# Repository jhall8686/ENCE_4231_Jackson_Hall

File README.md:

# ENCE_4231_Jackson_Hall
Embedded Systems Repository

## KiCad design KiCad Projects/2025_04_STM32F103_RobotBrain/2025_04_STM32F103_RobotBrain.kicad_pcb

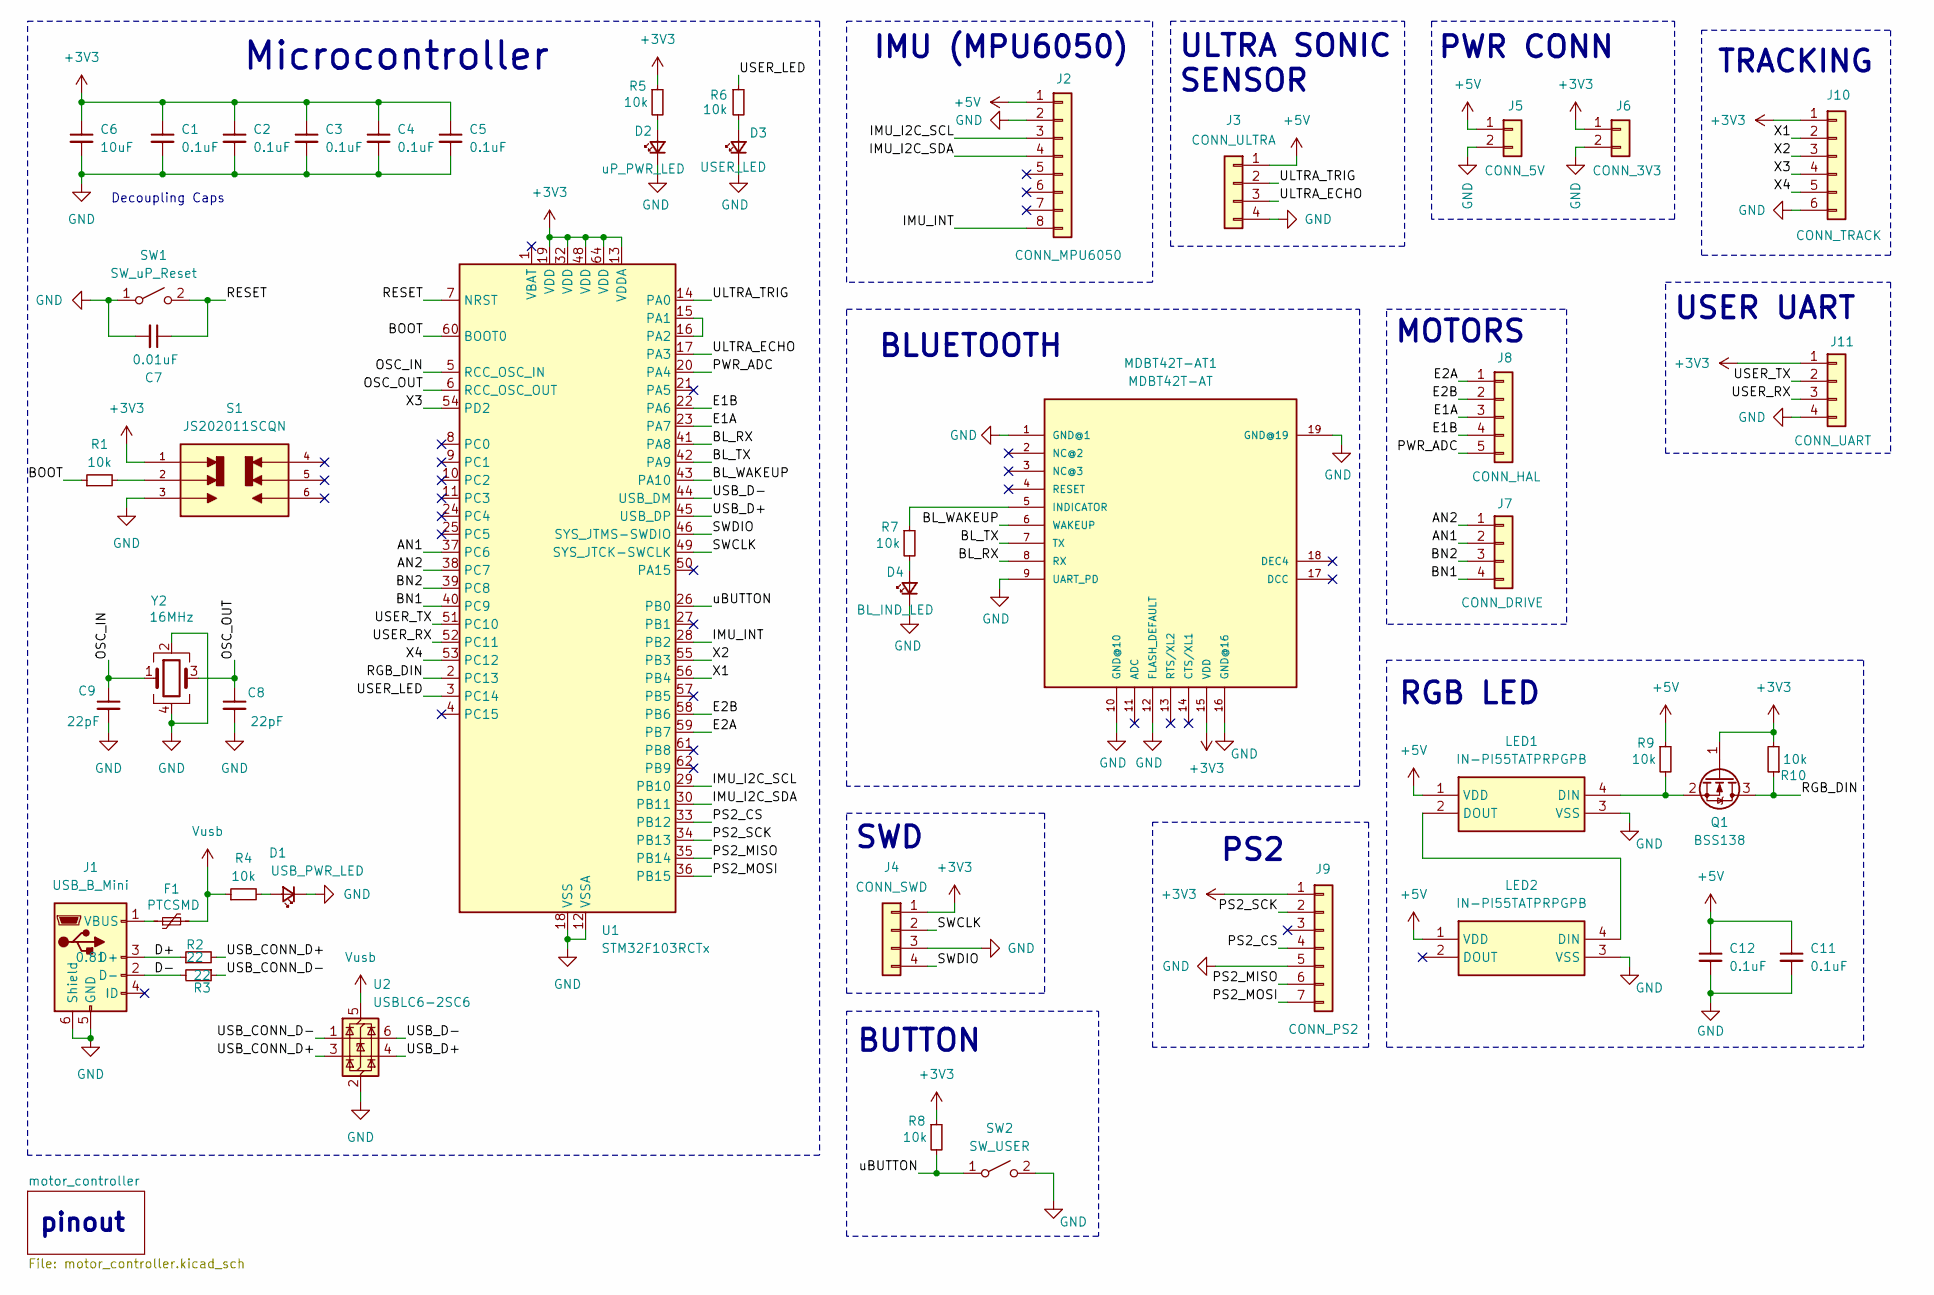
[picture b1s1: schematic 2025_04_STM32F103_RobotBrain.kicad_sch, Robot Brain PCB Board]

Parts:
C1, C2, C3, C4, C5, C11, C12: 0.1uF; C_0805_2012Metric_Pad1.18x1.45mm_HandSolder; Mfr #P KAM21BR71H104JT
C6: 10uF; C_0805_2012Metric_Pad1.18x1.45mm_HandSolder; Mfr #P LMK212ABJ106KG-T
C7: 0.01uF; C_0805_2012Metric_Pad1.18x1.45mm_HandSolder; Mfr #P KAF21BR72A103JT
C8, C9: 22pF; C_0805_2012Metric_Pad1.18x1.45mm_HandSolder; Mfr #P 0805ZA220JAT2A
D1: USB_PWR_LED; LED_0805_2012Metric_Pad1.15x1.40mm_HandSolder; Mfr #P 150080VS75000
D2: uP_PWR_LED; LED_0805_2012Metric_Pad1.15x1.40mm_HandSolder; Mfr #P 150080VS75000
D3: USER_LED; LED_0805_2012Metric_Pad1.15x1.40mm_HandSolder; Mfr #P 150080RS75000
D4: BL_IND_LED; LED_0805_2012Metric_Pad1.15x1.40mm_HandSolder; Mfr #P 150080VS75000
F1: PTCSMD; Fuse_0805_2012Metric_Pad1.15x1.40mm_HandSolder; Mfr #P 0ZCK0050AF2E
J1: USB_B_Mini; USB_Mini-B_Lumberg_2486_01_Horizontal; Mfr #P UJ2-MBH-4-SMT-TR
J2: CONN_MPU6050; PinSocket_1x08_P2.54mm_Vertical
J3: CONN_ULTRA; PinSocket_1x04_P2.54mm_Vertical
J4: CONN_SWD; PinSocket_1x04_P2.54mm_Vertical
J5: CONN_5V; JST_XH_B2B-XH-A_1x02_P2.50mm_Vertical
J6: CONN_3V3; JST_XH_B2B-XH-A_1x02_P2.50mm_Vertical
J7: CONN_DRIVE; JST_XH_B4B-XH-A_1x04_P2.50mm_Vertical
J8: CONN_HAL; JST_XH_B5B-XH-A_1x05_P2.50mm_Vertical
J9: CONN_PS2; PinHeader_1x07_P2.54mm_Vertical
J10: CONN_TRACK; JST_XH_B6B-XH-A_1x06_P2.50mm_Vertical
J11: CONN_UART; JST_XH_B4B-XH-A_1x04_P2.50mm_Vertical
LED1, LED2: IN-PI55TATPRPGPB; INPI55TATPRPGPB; Manufacturer_Part_Number IN-PI55TATPRPGPB; Mouser Part Number 743-IN-PI55TATPRPGPB
MDBT42T-AT1: MDBT42T-AT; MDBT42T
Q1: BSS138; SOT-23; Mfr #P BSS138
R1, R4, R5, R6, R7, R8, R9, R10: 10k; R_0805_2012Metric_Pad1.20x1.40mm_HandSolder; Mfr #P RK73B2ATTE103J
R2, R3: 22; R_0805_2012Metric_Pad1.20x1.40mm_HandSolder; Mfr #P RC0805FR-7W22RL
S1: JS202011SCQN; SW_uP_Boot; PARTREV 26 May 22
SW1: SW_uP_Reset; Mfr #P 434121025816
SW2: SW_USER; SW_SPST_PTS647_Sx50; Mfr #P TL3305BF100QG
U1: STM32F103RCTx; LQFP-64_10x10mm_P0.5mm; Mfr #P STM32F103RCT6
U2: USBLC6-2SC6; SOT-23-6; Mfr #P USBLC6-2SC6
Y2: 16MHz; Crystal_SMD_Abracon_ABM8G-4Pin_3.2x2.5mm; Mfr #P ABM8-16.000MHZ-D1X-T

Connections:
+3V3: C1.1, C2.1, C3.1, C4.1, C5.1, C6.1, J4.1, J6.1, J9.1, J10.1, J11.1, MDBT42T-AT1.15 (VDD), Q1.1 (G), R5.1, R8.1, R10.2, S1.1, U1.13 (VDDA), U1.19 (VDD), U1.32 (VDD), U1.48 (VDD), U1.64 (VDD)
+5V: C11.1, C12.1, J2.1, J3.1, J5.1, LED1.1 (VDD), LED2.1 (VDD), R9.1
/AN1: J7.2, U1.37 (PC6)
/AN2: J7.1, U1.38 (PC7)
/BL_RX: MDBT42T-AT1.8 (RX), U1.41 (PA8)
/BL_TX: MDBT42T-AT1.7 (TX), U1.42 (PA9)
/BL_WAKEUP: MDBT42T-AT1.6 (WAKEUP), U1.43 (PA10)
/BN1: J7.4, U1.40 (PC9)
/BN2: J7.3, U1.39 (PC8)
/BOOT: R1.1, U1.60 (BOOT0)
/D+: J1.3 (D+), R2.1
/D-: J1.2 (D-), R3.2
/E1A: J8.3, U1.23 (PA7)
/E1B: J8.4, U1.22 (PA6)
/E2A: J8.1, U1.59 (PB7)
/E2B: J8.2, U1.58 (PB6)
/IMU_I2C_SCL: J2.3, U1.29 (PB10)
/IMU_I2C_SDA: J2.4, U1.30 (PB11)
/IMU_INT: J2.8, U1.28 (PB2)
/OSC_IN: C9.1, U1.5 (RCC_OSC_IN), Y2.1
/OSC_OUT: C8.1, U1.6 (RCC_OSC_OUT), Y2.3
/PS2_CS: J9.4, U1.33 (PB12)
/PS2_MISO: J9.6, U1.35 (PB14)
/PS2_MOSI: J9.7, U1.36 (PB15)
/PS2_SCK: J9.2, U1.34 (PB13)
/PWR_ADC: J8.5, U1.20 (PA4)
/RESET: C7.1, SW1.2 (B), U1.7 (NRST)
/RGB_DIN: Q1.3 (D), R10.1, U1.2 (PC13)
/SWCLK: J4.2, U1.49 (SYS_JTCK-SWCLK)
/SWDIO: J4.4, U1.46 (SYS_JTMS-SWDIO)
/ULTRA_ECHO: J3.3, U1.17 (PA3)
/ULTRA_TRIG: J3.2, U1.14 (PA0)
/USB_CONN_D+: R2.2, U2.3 (I/O2)
/USB_CONN_D-: R3.1, U2.1 (I/O1)
/USB_D+: U1.45 (USB_DP), U2.4 (I/O2)
/USB_D-: U1.44 (USB_DM), U2.6 (I/O1)
/USER_LED: R6.1, U1.3 (PC14)
/USER_RX: J11.3, U1.52 (PC11)
/USER_TX: J11.2, U1.51 (PC10)
/X1: J10.2, U1.56 (PB4)
/X2: J10.3, U1.55 (PB3)
/X3: J10.4, U1.54 (PD2)
/X4: J10.5, U1.53 (PC12)
/uBUTTON: R8.2, SW2.1 (A), U1.26 (PB0)
GND: C1.2, C2.2, C3.2, C4.2, C5.2, C6.2, C7.2, C8.2, C9.2, C11.2, C12.2, D1.1 (K), D2.1 (K), D3.1 (K), D4.1 (K), J1.5 (GND), J1.6 (Shield), J2.2, J3.4, J4.3, J5.2, J6.2, J9.5, J10.6, J11.4, LED1.3 (VSS), LED2.3 (VSS), MDBT42T-AT1.1 (GND@1), MDBT42T-AT1.9 (UART_PD), MDBT42T-AT1.10 (GND@10), MDBT42T-AT1.12 (FLASH_DEFAULT), MDBT42T-AT1.16 (GND@16), MDBT42T-AT1.19 (GND@19), S1.3, SW1.1 (A), SW2.2 (B), U1.12 (VSSA), U1.18 (VSS), U1.31 (VSS), U1.47 (VSS), U1.63 (VSS), U2.2 (GND), Y2.2, Y2.4
unnamed: D1.2 (A), R4.2
unnamed: D2.2 (A), R5.2
unnamed: D3.2 (A), R6.2
unnamed: D4.2 (A), R7.2
unnamed: F1.1, J1.1 (VBUS)
unnamed: LED1.4 (DIN), Q1.2 (S), R9.2
unnamed: LED1.2 (DOUT), LED2.4 (DIN)
unnamed: MDBT42T-AT1.5 (INDICATOR), R7.1
unnamed: R1.2, S1.2
unnamed: U1.15 (PA1), U1.16 (PA2)
Vusb: F1.2, R4.1, U2.5 (VBUS)

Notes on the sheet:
PWR CONN
ULTRA SONIC SENSOR
Decoupling Caps
BUTTON
MOTORS
PS2
RGB LED
Microcontroller
TRACKING
pinout
IMU (MPU6050)
SWD
USER UART
BLUETOOTH

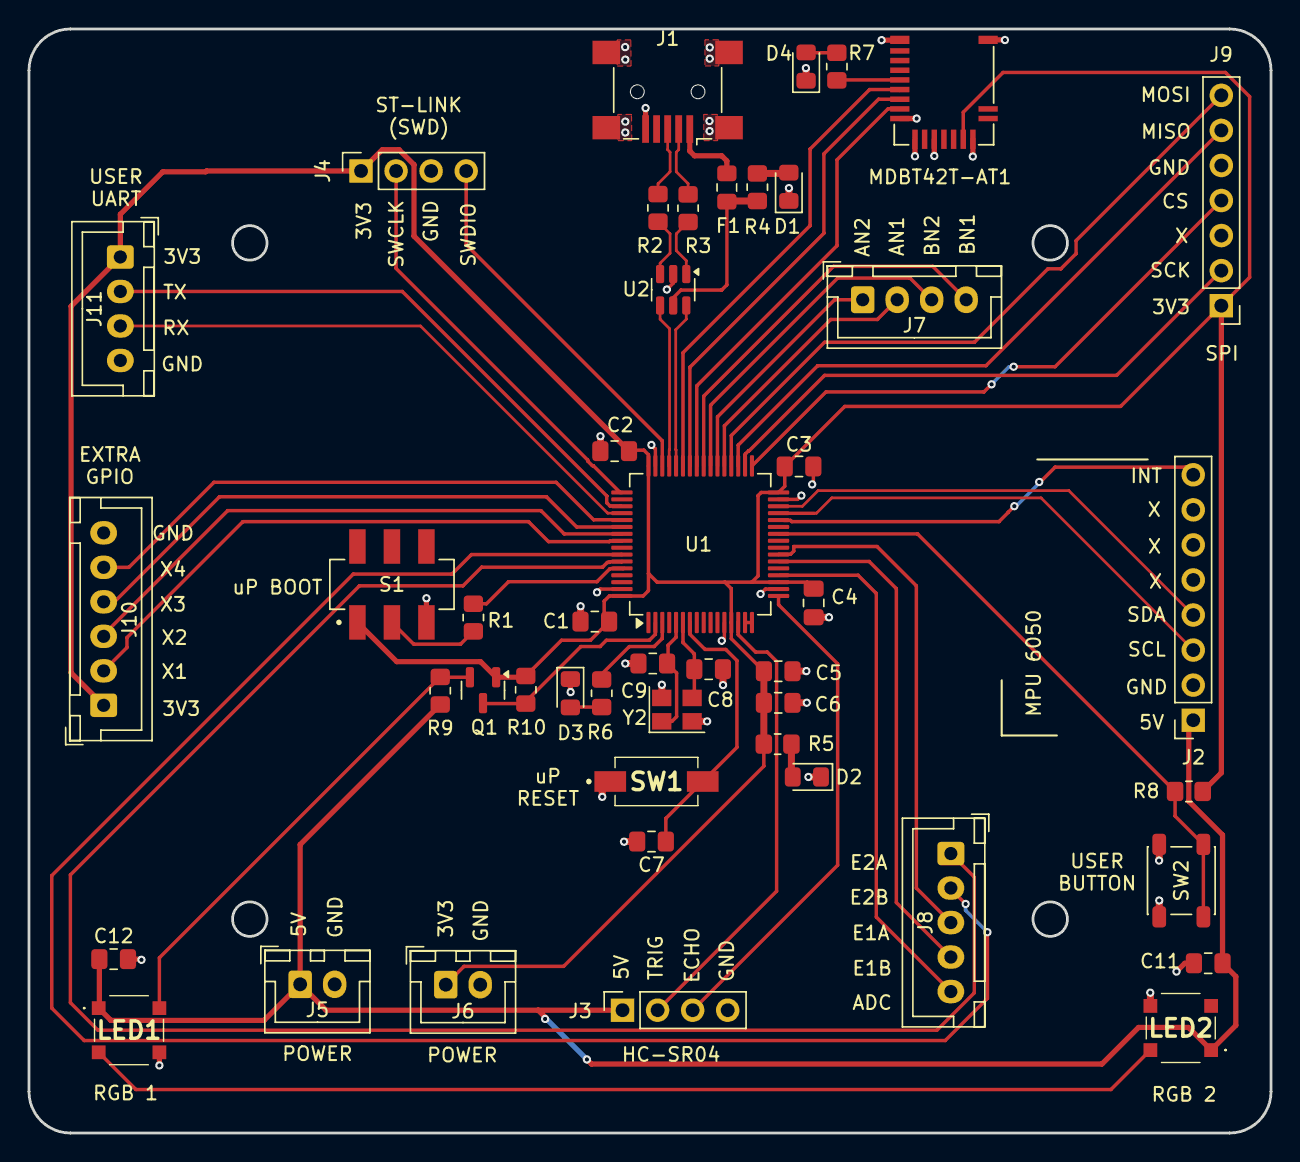
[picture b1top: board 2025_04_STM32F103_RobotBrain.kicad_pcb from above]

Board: 2 copper layers, 90.0 x 80.0 mm, 47 parts (0 on the bottom side), 56 nets.

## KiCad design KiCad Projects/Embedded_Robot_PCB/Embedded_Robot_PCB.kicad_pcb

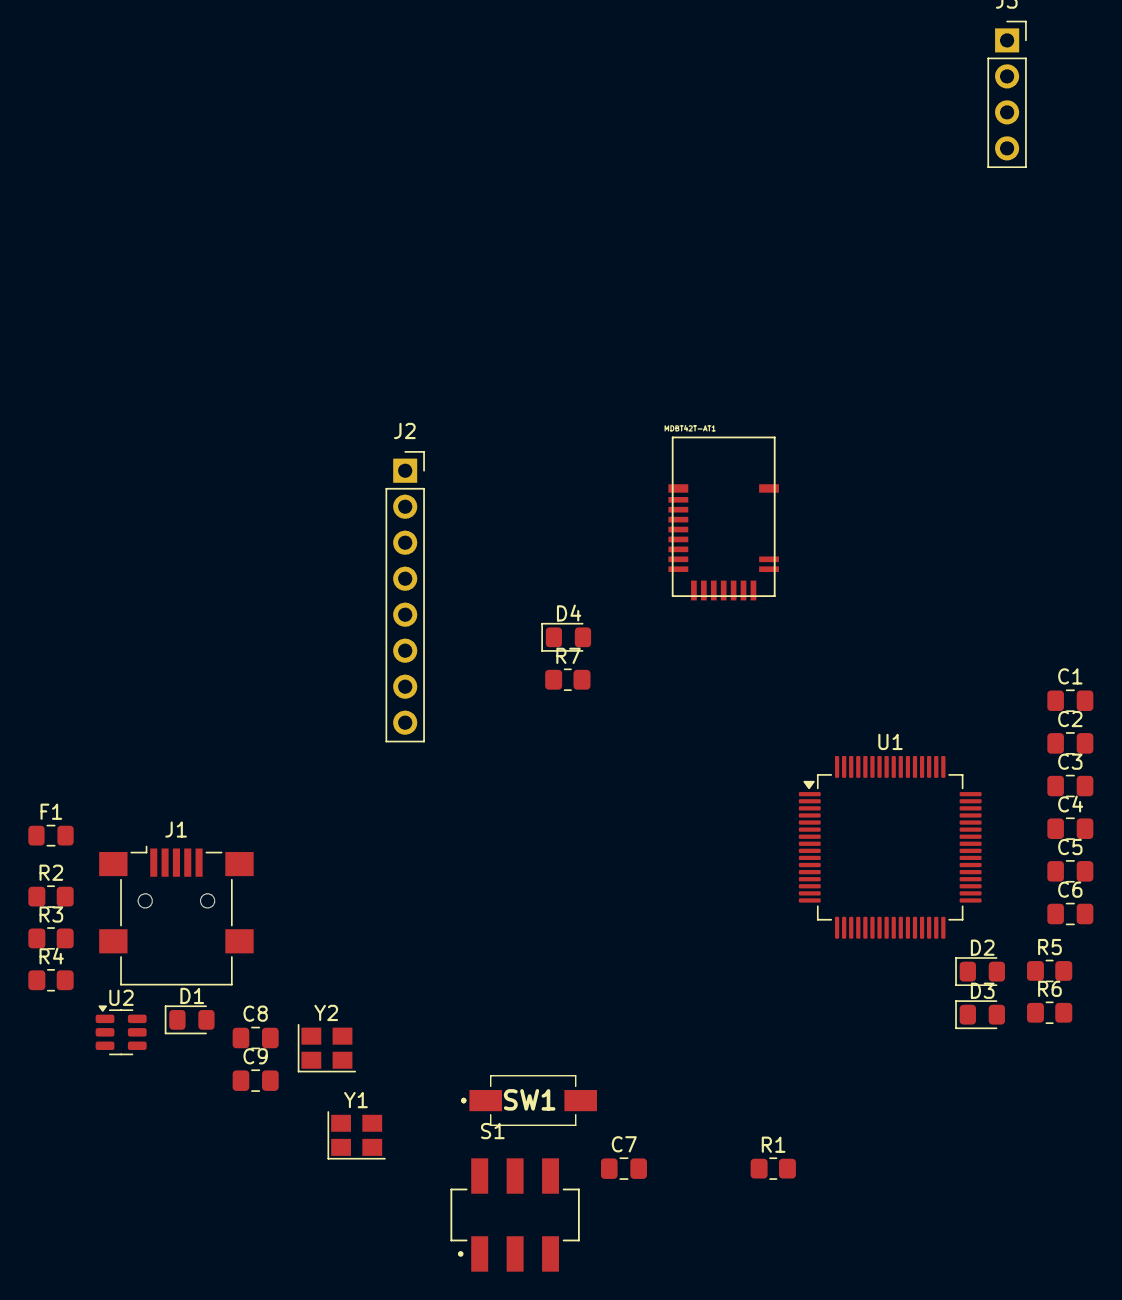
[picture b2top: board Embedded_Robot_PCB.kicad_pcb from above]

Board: 2 copper layers, 31 parts (0 on the bottom side), 21 nets, no tracks yet.

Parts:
C1, C2, C3, C4, C5: 0.1uF; C_0805_2012Metric_Pad1.18x1.45mm_HandSolder
C6: 10uF; C_0805_2012Metric_Pad1.18x1.45mm_HandSolder
C7: 0.01uF; C_0805_2012Metric_Pad1.18x1.45mm_HandSolder
C8, C9: 22pF; C_0805_2012Metric_Pad1.18x1.45mm_HandSolder
D1: USB_PWR_LED; LED_0805_2012Metric_Pad1.15x1.40mm_HandSolder
D2: BL_IND_LED; LED_0805_2012Metric_Pad1.15x1.40mm_HandSolder
D3: USER_LED; LED_0805_2012Metric_Pad1.15x1.40mm_HandSolder
D4: uP_PWR_LED; LED_0805_2012Metric_Pad1.15x1.40mm_HandSolder
F1: PTCSMD; Fuse_0805_2012Metric_Pad1.15x1.40mm_HandSolder
J1: USB_B_Mini; USB_Mini-B_Lumberg_2486_01_Horizontal
J2: CONN_MPU6050; PinSocket_1x08_P2.54mm_Vertical
J3: CONN_ULTRA; PinSocket_1x04_P2.54mm_Vertical
MDBT42T-AT1: MDBT42T-AT; MDBT42T
R1, R4, R5, R6, R7: 10k; R_0805_2012Metric_Pad1.20x1.40mm_HandSolder
R2, R3: 22; R_0805_2012Metric_Pad1.20x1.40mm_HandSolder
S1: SW_uP_Boot; SW_JS202011SCQN
SW1: SW_uP_Reset
U1: STM32F103RCTx; LQFP-64_10x10mm_P0.5mm
U2: USBLC6-2SC6; SOT-23-6
Y1: Crystal_GND23; Crystal_SMD_Abracon_ABM8G-4Pin_3.2x2.5mm
Y2: 16MHz; Crystal_SMD_Abracon_ABM8G-4Pin_3.2x2.5mm

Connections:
+3V3: C1.1, C2.1, C3.1, C4.1, C5.1, C6.1, MDBT42T-AT1.15 (VDD), R7.1, S1.1, U1.13 (VDDA), U1.19 (VDD), U1.32 (VDD), U1.48 (VDD), U1.64 (VDD)
+5V: J2.1, J3.4
/BOOT: R1.1, U1.60 (BOOT0)
/D+: J1.3 (D+), R3.1
/D-: J1.2 (D-), R2.1
/OSC_IN: C9.2, U1.5 (RCC_OSC_IN), Y2.1
/OSC_OUT: C8.2, U1.6 (RCC_OSC_OUT), Y2.3
/RESET: C7.2, SW1.2 (B), U1.7 (NRST)
/USB_CONN_D+: R3.2, U2.3 (I/O2)
/USB_CONN_D-: R2.2, U2.1 (I/O1)
/USB_D+: U1.45 (USB_DP), U2.4 (I/O2)
/USB_D-: U1.44 (USB_DM), U2.6 (I/O1)
GND: C1.2, C2.2, C3.2, C4.2, C5.2, C6.2, C7.1, C8.1, C9.1, D1.1 (K), D2.1 (K), D3.1 (K), D4.1 (K), J1.5 (GND), J2.2, J3.1, MDBT42T-AT1.1 (GND@1), MDBT42T-AT1.9 (UART_PD), MDBT42T-AT1.10 (GND@10), MDBT42T-AT1.12 (FLASH_DEFAULT), MDBT42T-AT1.16 (GND@16), MDBT42T-AT1.19 (GND@19), S1.3, SW1.1 (A), U1.12 (VSSA), U1.18 (VSS), U1.31 (VSS), U1.47 (VSS), U1.63 (VSS), U2.2 (GND), Y2.2, Y2.4
unnamed: D1.2 (A), R4.2
unnamed: D2.2 (A), R5.2
unnamed: D3.2 (A), R6.2
unnamed: D4.2 (A), R7.2
unnamed: F1.2, J1.1 (VBUS)
unnamed: MDBT42T-AT1.5 (INDICATOR), R5.1
unnamed: R1.2, S1.2
Vusb: F1.1, R4.1, U2.5 (VBUS)

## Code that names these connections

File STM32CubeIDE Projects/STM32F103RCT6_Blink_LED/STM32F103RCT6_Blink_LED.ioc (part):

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Mcu.Name=STM32F103R(C-D-E)Tx
Mcu.Package=LQFP64
Mcu.UserName=STM32F103RCTx
PA10.Mode=Asynchronous
PA10.Signal=USART1_RX
PA11.Mode=Device
PA11.Signal=USB_DM
PA12.Mode=Device
PA12.Signal=USB_DP
PA13.Mode=Serial_Wire
PA13.Signal=SYS_JTMS-SWDIO
PA14.Mode=Serial_Wire
PA14.Signal=SYS_JTCK-SWCLK
PA4.GPIOParameters=GPIO_Label
PA4.GPIO_Label=PWR_ADC
PA4.Signal=ADCx_IN4
PA7.GPIOParameters=GPIO_Label
PA7.GPIO_Label=RGB_DIN
PA7.Signal=GPIO_Output
PA8.GPIOParameters=GPIO_Label
PA8.GPIO_Label=BL_WAKEUP
PA8.Signal=GPIO_Output
PA9.Mode=Asynchronous
PA9.Signal=USART1_TX
PB0.GPIOParameters=GPIO_Label
PB0.GPIO_Label=USER_BUTTON
PB0.Signal=GPIO_Input
PB13.Mode=Full_Duplex_Master
PB13.Signal=SPI2_SCK
PB14.Mode=Full_Duplex_Master
PB14.Signal=SPI2_MISO
PB15.Mode=Full_Duplex_Master
PB15.Signal=SPI2_MOSI
PB5.Signal=GPIO_Input
PB6.Mode=I2C
PB6.Signal=I2C1_SCL
PB7.Mode=I2C
PB7.Signal=I2C1_SDA
PC13-TAMPER-RTC.GPIOParameters=GPIO_Label
PC13-TAMPER-RTC.GPIO_Label=USER_LED
PC13-TAMPER-RTC.Signal=GPIO_Output
PC14-OSC32_IN.Signal=GPIO_Output
PD0-OSC_IN.Mode=HSE-External-Oscillator
PD0-OSC_IN.Signal=RCC_OSC_IN
PD1-OSC_OUT.Mode=HSE-External-Oscillator
PD1-OSC_OUT.Signal=RCC_OSC_OUT
board=custom

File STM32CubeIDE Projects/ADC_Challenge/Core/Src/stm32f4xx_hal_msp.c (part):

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
    __HAL_RCC_GPIOA_CLK_ENABLE();
    /**ADC1 GPIO Configuration
    PA1     ------> ADC1_IN1
    */
    GPIO_InitStruct.Pin = GPIO_PIN_1;
    GPIO_InitStruct.Mode = GPIO_MODE_ANALOG;
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    __HAL_RCC_ADC1_CLK_DISABLE();

    /**ADC1 GPIO Configuration
    PA1     ------> ADC1_IN1
    */
    HAL_GPIO_DeInit(GPIOA, GPIO_PIN_1);

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
    __HAL_RCC_GPIOB_CLK_ENABLE();
    /**I2C1 GPIO Configuration
    PB6     ------> I2C1_SCL
    PB9     ------> I2C1_SDA
    */
    GPIO_InitStruct.Pin = Audio_SCL_Pin|Audio_SDA_Pin;
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    __HAL_RCC_I2C1_CLK_DISABLE();

    /**I2C1 GPIO Configuration
    PB6     ------> I2C1_SCL
    PB9     ------> I2C1_SDA
    */
    HAL_GPIO_DeInit(Audio_SCL_GPIO_Port, Audio_SCL_Pin);
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    __HAL_RCC_GPIOA_CLK_ENABLE();
    __HAL_RCC_GPIOC_CLK_ENABLE();
    /**I2S3 GPIO Configuration
    PA4     ------> I2S3_WS
    PC7     ------> I2S3_MCK
    PC10     ------> I2S3_CK
    PC12     ------> I2S3_SD
    */
    GPIO_InitStruct.Pin = I2S3_WS_Pin;
    GPIO_InitStruct.Mode = GPIO_MODE_AF_PP;
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    __HAL_RCC_SPI3_CLK_DISABLE();

    /**I2S3 GPIO Configuration
    PA4     ------> I2S3_WS
    PC7     ------> I2S3_MCK
    PC10     ------> I2S3_CK
    PC12     ------> I2S3_SD
    */
    HAL_GPIO_DeInit(I2S3_WS_GPIO_Port, I2S3_WS_Pin);

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    __HAL_RCC_GPIOA_CLK_ENABLE();
    /**SPI1 GPIO Configuration
    PA5     ------> SPI1_SCK
    PA6     ------> SPI1_MISO
    PA7     ------> SPI1_MOSI
    */
    GPIO_InitStruct.Pin = SPI1_SCK_Pin|SPI1_MISO_Pin|SPI1_MOSI_Pin;
    GPIO_InitStruct.Mode = GPIO_MODE_AF_PP;
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
    /**SPI1 GPIO Configuration
    PA5     ------> SPI1_SCK
    PA6     ------> SPI1_MISO
    PA7     ------> SPI1_MOSI
    */
    HAL_GPIO_DeInit(GPIOA, SPI1_SCK_Pin|SPI1_MISO_Pin|SPI1_MOSI_Pin);

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
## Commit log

2025-04-04 Commit 4/4/25
2025-04-09 PCB v1
2025-04-17 Commit 4/17 Including Ultrasonic Sensor Challenge
2025-04-17 Commit 4/17
2025-04-23 Commit 4/23
2025-04-24 4/24 Inclass Work
2025-05-04 Routing
2025-05-05 Routing Complete
2025-05-06 PCB Complete (with Gerber)
2025-05-20 ADC Challenge & Updates
2025-05-28 Haven't in a while

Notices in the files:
STM32CubeIDE Projects/ADC_Challenge/Core/Src/stm32f4xx_hal_msp.c:
Copyright (c) 2025 STMicroelectronics.
All rights reserved.
This software is licensed under terms that can be found in the LICENSE file
